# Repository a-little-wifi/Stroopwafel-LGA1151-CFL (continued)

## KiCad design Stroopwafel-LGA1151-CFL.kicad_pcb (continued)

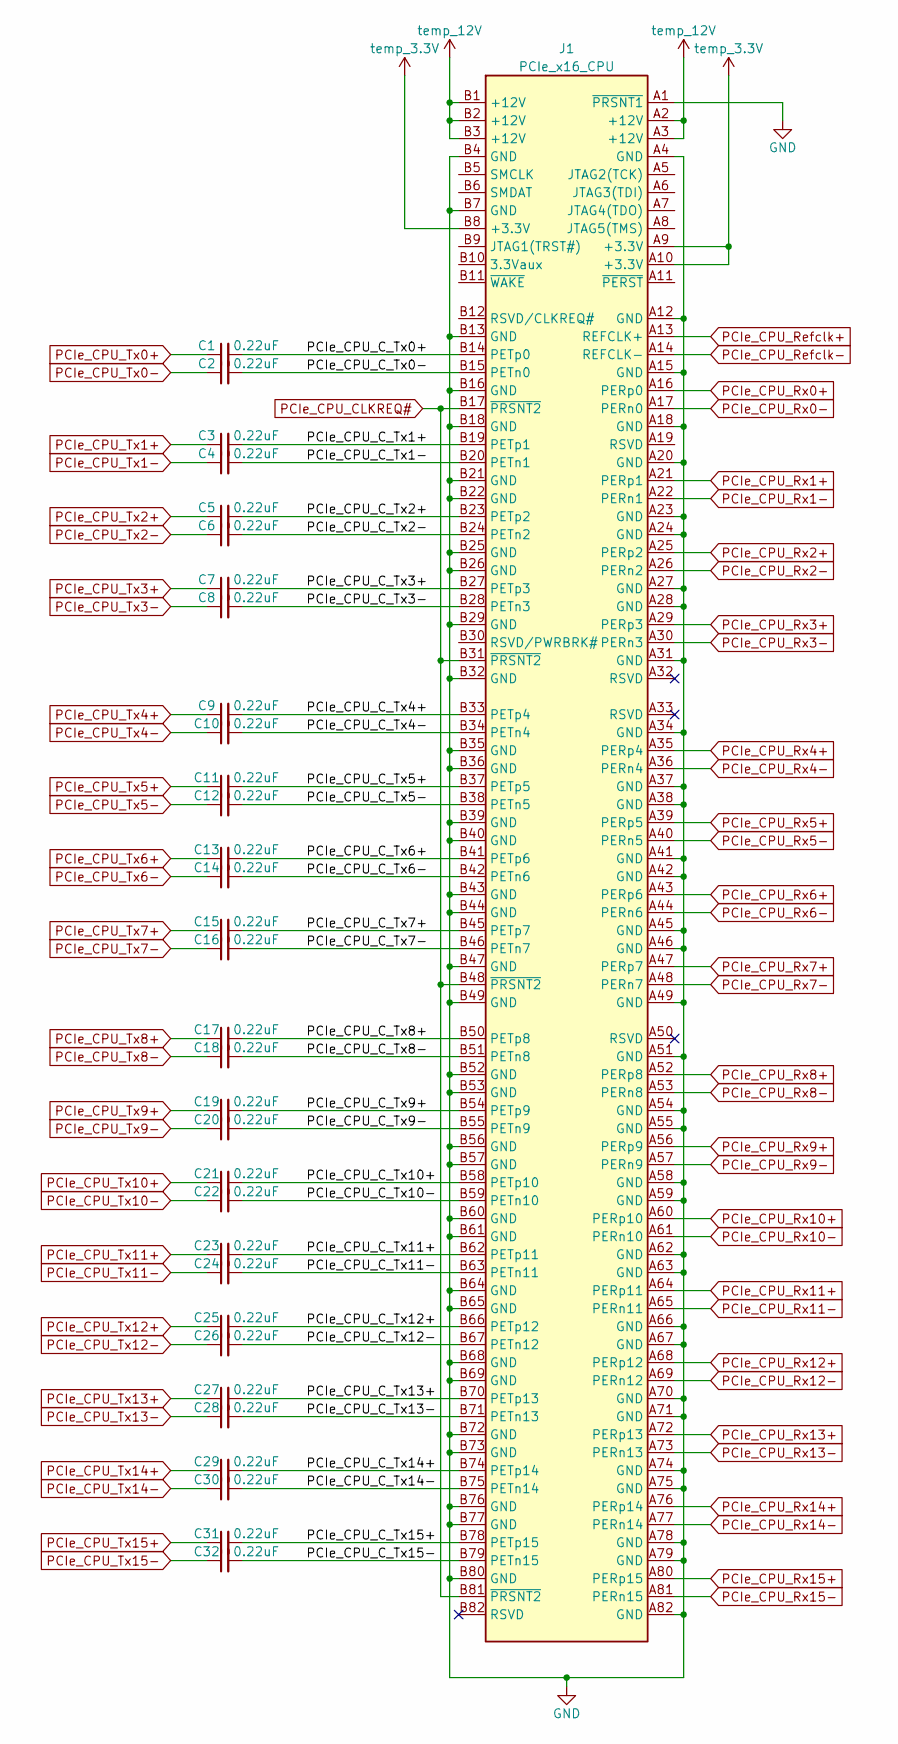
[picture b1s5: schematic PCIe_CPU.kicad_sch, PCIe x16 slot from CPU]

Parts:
C1, C2, C3, C4, C5, C6, C7, C8, C9, C10, C11, C12, C13, C14, C15, C16, C17, C18, C19, C20, C21, C22, C23, C24, C25, C26, C27, C28, C29, C30, C31, C32: 0.22uF; C_0402_1005Metric
J1: PCIe_x16_CPU; PCIe_x16_tht_smallholes

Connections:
/PCIe_CPU/PCIe_CPU_C_Tx0+: C1.2, J1.B14 (PETp0)
/PCIe_CPU/PCIe_CPU_C_Tx0-: C2.2, J1.B15 (PETn0)
/PCIe_CPU/PCIe_CPU_C_Tx1+: C3.2, J1.B19 (PETp1)
/PCIe_CPU/PCIe_CPU_C_Tx1-: C4.2, J1.B20 (PETn1)
/PCIe_CPU/PCIe_CPU_C_Tx2+: C5.2, J1.B23 (PETp2)
/PCIe_CPU/PCIe_CPU_C_Tx2-: C6.2, J1.B24 (PETn2)
/PCIe_CPU/PCIe_CPU_C_Tx3+: C7.2, J1.B27 (PETp3)
/PCIe_CPU/PCIe_CPU_C_Tx3-: C8.2, J1.B28 (PETn3)
/PCIe_CPU/PCIe_CPU_C_Tx4+: C9.2, J1.B33 (PETp4)
/PCIe_CPU/PCIe_CPU_C_Tx4-: C10.2, J1.B34 (PETn4)
/PCIe_CPU/PCIe_CPU_C_Tx5+: C11.2, J1.B37 (PETp5)
/PCIe_CPU/PCIe_CPU_C_Tx5-: C12.2, J1.B38 (PETn5)
/PCIe_CPU/PCIe_CPU_C_Tx6+: C13.2, J1.B41 (PETp6)
/PCIe_CPU/PCIe_CPU_C_Tx6-: C14.2, J1.B42 (PETn6)
/PCIe_CPU/PCIe_CPU_C_Tx7+: C15.2, J1.B45 (PETp7)
/PCIe_CPU/PCIe_CPU_C_Tx7-: C16.2, J1.B46 (PETn7)
/PCIe_CPU/PCIe_CPU_C_Tx8+: C17.2, J1.B50 (PETp8)
/PCIe_CPU/PCIe_CPU_C_Tx8-: C18.2, J1.B51 (PETn8)
/PCIe_CPU/PCIe_CPU_C_Tx9+: C19.2, J1.B54 (PETp9)
/PCIe_CPU/PCIe_CPU_C_Tx9-: C20.2, J1.B55 (PETn9)
/PCIe_CPU/PCIe_CPU_C_Tx10+: C21.2, J1.B58 (PETp10)
/PCIe_CPU/PCIe_CPU_C_Tx10-: C22.2, J1.B59 (PETn10)
/PCIe_CPU/PCIe_CPU_C_Tx11+: C23.2, J1.B62 (PETp11)
/PCIe_CPU/PCIe_CPU_C_Tx11-: C24.2, J1.B63 (PETn11)
/PCIe_CPU/PCIe_CPU_C_Tx12+: C25.2, J1.B66 (PETp12)
/PCIe_CPU/PCIe_CPU_C_Tx12-: C26.2, J1.B67 (PETn12)
/PCIe_CPU/PCIe_CPU_C_Tx13+: C27.2, J1.B70 (PETp13)
/PCIe_CPU/PCIe_CPU_C_Tx13-: C28.2, J1.B71 (PETn13)
/PCIe_CPU/PCIe_CPU_C_Tx14+: C29.2, J1.B74 (PETp14)
/PCIe_CPU/PCIe_CPU_C_Tx14-: C30.2, J1.B75 (PETn14)
/PCIe_CPU/PCIe_CPU_C_Tx15+: C31.2, J1.B78 (PETp15)
/PCIe_CPU/PCIe_CPU_C_Tx15-: C32.2, J1.B79 (PETn15)
GND: J1.A1 (~PRSNT1), J1.A4 (GND), J1.A12 (GND), J1.A15 (GND), J1.A18 (GND), J1.A20 (GND), J1.A23 (GND), J1.A24 (GND), J1.A27 (GND), J1.A28 (GND), J1.A31 (GND), J1.A34 (GND), J1.A37 (GND), J1.A38 (GND), J1.A41 (GND), J1.A42 (GND), J1.A45 (GND), J1.A46 (GND), J1.A49 (GND), J1.A51 (GND), J1.A54 (GND), J1.A55 (GND), J1.A58 (GND), J1.A59 (GND), J1.A62 (GND), J1.A63 (GND), J1.A66 (GND), J1.A67 (GND), J1.A70 (GND), J1.A71 (GND), J1.A74 (GND), J1.A75 (GND), J1.A78 (GND), J1.A79 (GND), J1.A82 (GND), J1.B4 (GND), J1.B7 (GND), J1.B13 (GND), J1.B16 (GND), J1.B18 (GND), J1.B21 (GND), J1.B22 (GND), J1.B25 (GND), J1.B26 (GND), J1.B29 (GND), J1.B32 (GND), J1.B35 (GND), J1.B36 (GND), J1.B39 (GND), J1.B40 (GND), J1.B43 (GND), J1.B44 (GND), J1.B47 (GND), J1.B49 (GND), J1.B52 (GND), J1.B53 (GND), J1.B56 (GND), J1.B57 (GND), J1.B60 (GND), J1.B61 (GND), J1.B64 (GND), J1.B65 (GND), J1.B68 (GND), J1.B69 (GND), J1.B72 (GND), J1.B73 (GND), J1.B76 (GND), J1.B77 (GND), J1.B80 (GND); also elsewhere on the board
PCIe_CPU_CLKREQ#: J1.B17 (~PRSNT2), J1.B31 (~PRSNT2), J1.B48 (~PRSNT2), J1.B81 (~PRSNT2); also elsewhere on the board
PCIe_CPU_Refclk+: J1.A13 (REFCLK+); also elsewhere on the board
PCIe_CPU_Refclk-: J1.A14 (REFCLK-); also elsewhere on the board
PCIe_CPU_Rx0+: J1.A16 (PERp0); also elsewhere on the board
PCIe_CPU_Rx0-: J1.A17 (PERn0); also elsewhere on the board
PCIe_CPU_Rx1+: J1.A21 (PERp1); also elsewhere on the board
PCIe_CPU_Rx1-: J1.A22 (PERn1); also elsewhere on the board
PCIe_CPU_Rx2+: J1.A25 (PERp2); also elsewhere on the board
PCIe_CPU_Rx2-: J1.A26 (PERn2); also elsewhere on the board
PCIe_CPU_Rx3+: J1.A29 (PERp3); also elsewhere on the board
PCIe_CPU_Rx3-: J1.A30 (PERn3); also elsewhere on the board
PCIe_CPU_Rx4+: J1.A35 (PERp4); also elsewhere on the board
PCIe_CPU_Rx4-: J1.A36 (PERn4); also elsewhere on the board
PCIe_CPU_Rx5+: J1.A39 (PERp5); also elsewhere on the board
PCIe_CPU_Rx5-: J1.A40 (PERn5); also elsewhere on the board
PCIe_CPU_Rx6+: J1.A43 (PERp6); also elsewhere on the board
PCIe_CPU_Rx6-: J1.A44 (PERn6); also elsewhere on the board
PCIe_CPU_Rx7+: J1.A47 (PERp7); also elsewhere on the board
PCIe_CPU_Rx7-: J1.A48 (PERn7); also elsewhere on the board
PCIe_CPU_Rx8+: J1.A52 (PERp8); also elsewhere on the board
PCIe_CPU_Rx8-: J1.A53 (PERn8); also elsewhere on the board
PCIe_CPU_Rx9+: J1.A56 (PERp9); also elsewhere on the board
PCIe_CPU_Rx9-: J1.A57 (PERn9); also elsewhere on the board
PCIe_CPU_Rx10+: J1.A60 (PERp10); also elsewhere on the board
PCIe_CPU_Rx10-: J1.A61 (PERn10); also elsewhere on the board
PCIe_CPU_Rx11+: J1.A64 (PERp11); also elsewhere on the board
PCIe_CPU_Rx11-: J1.A65 (PERn11); also elsewhere on the board
PCIe_CPU_Rx12+: J1.A68 (PERp12); also elsewhere on the board
PCIe_CPU_Rx12-: J1.A69 (PERn12); also elsewhere on the board
PCIe_CPU_Rx13+: J1.A72 (PERp13); also elsewhere on the board
PCIe_CPU_Rx13-: J1.A73 (PERn13); also elsewhere on the board
PCIe_CPU_Rx14+: J1.A76 (PERp14); also elsewhere on the board
PCIe_CPU_Rx14-: J1.A77 (PERn14); also elsewhere on the board
PCIe_CPU_Rx15+: J1.A80 (PERp15); also elsewhere on the board
PCIe_CPU_Rx15-: J1.A81 (PERn15); also elsewhere on the board
PCIe_CPU_Tx0+: C1.1; also elsewhere on the board
PCIe_CPU_Tx0-: C2.1; also elsewhere on the board
PCIe_CPU_Tx1+: C3.1; also elsewhere on the board
PCIe_CPU_Tx1-: C4.1; also elsewhere on the board
PCIe_CPU_Tx2+: C5.1; also elsewhere on the board
PCIe_CPU_Tx2-: C6.1; also elsewhere on the board
PCIe_CPU_Tx3+: C7.1; also elsewhere on the board
PCIe_CPU_Tx3-: C8.1; also elsewhere on the board
PCIe_CPU_Tx4+: C9.1; also elsewhere on the board
PCIe_CPU_Tx4-: C10.1; also elsewhere on the board
PCIe_CPU_Tx5+: C11.1; also elsewhere on the board
PCIe_CPU_Tx5-: C12.1; also elsewhere on the board
PCIe_CPU_Tx6+: C13.1; also elsewhere on the board
PCIe_CPU_Tx6-: C14.1; also elsewhere on the board
PCIe_CPU_Tx7+: C15.1; also elsewhere on the board
PCIe_CPU_Tx7-: C16.1; also elsewhere on the board
PCIe_CPU_Tx8+: C17.1; also elsewhere on the board
PCIe_CPU_Tx8-: C18.1; also elsewhere on the board
PCIe_CPU_Tx9+: C19.1; also elsewhere on the board
PCIe_CPU_Tx9-: C20.1; also elsewhere on the board
PCIe_CPU_Tx10+: C21.1; also elsewhere on the board
PCIe_CPU_Tx10-: C22.1; also elsewhere on the board
PCIe_CPU_Tx11+: C23.1; also elsewhere on the board
PCIe_CPU_Tx11-: C24.1; also elsewhere on the board
PCIe_CPU_Tx12+: C25.1; also elsewhere on the board
PCIe_CPU_Tx12-: C26.1; also elsewhere on the board
PCIe_CPU_Tx13+: C27.1; also elsewhere on the board
PCIe_CPU_Tx13-: C28.1; also elsewhere on the board
PCIe_CPU_Tx14+: C29.1; also elsewhere on the board
PCIe_CPU_Tx14-: C30.1; also elsewhere on the board
PCIe_CPU_Tx15+: C31.1; also elsewhere on the board
PCIe_CPU_Tx15-: C32.1; also elsewhere on the board
temp_3.3V: J1.A9 (+3.3V), J1.A10 (+3.3V), J1.B8 (+3.3V); also elsewhere on the board
temp_12V: J1.A2 (+12V), J1.A3 (+12V), J1.B1 (+12V), J1.B2 (+12V), J1.B3 (+12V); also elsewhere on the board

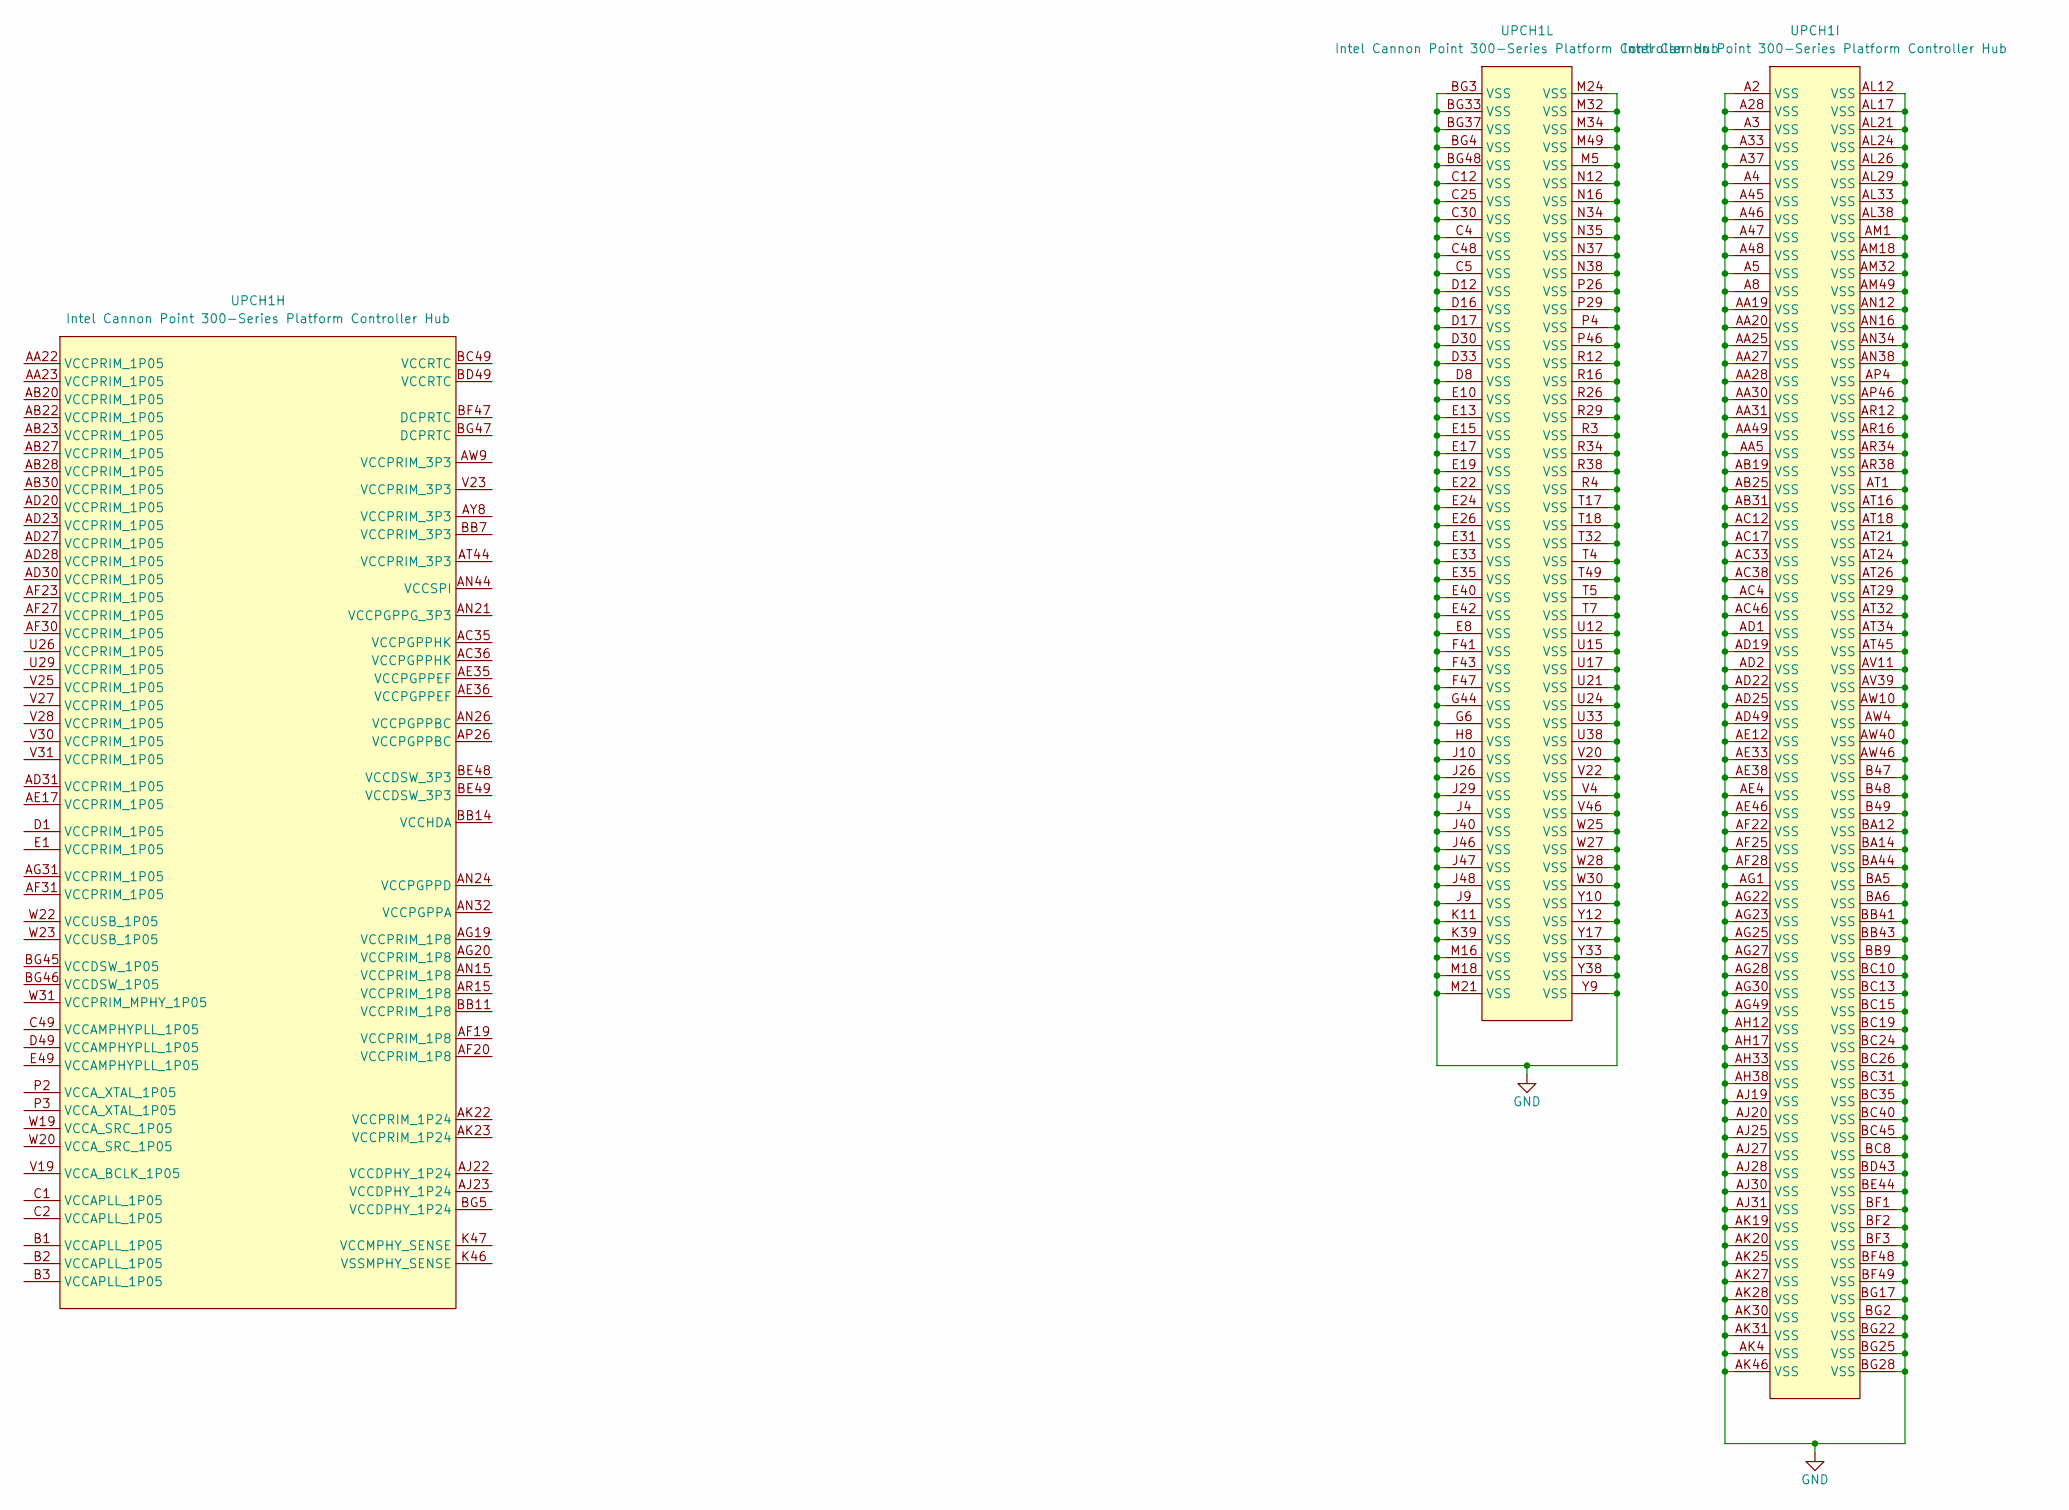
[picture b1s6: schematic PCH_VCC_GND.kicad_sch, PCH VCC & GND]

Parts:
UPCH1: Intel Cannon Point 300-Series Platform Controller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; CNP-H_BGA_874P-T

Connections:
GND: UPCH1.A2 (VSS), UPCH1.A3 (VSS), UPCH1.A4 (VSS), UPCH1.A5 (VSS), UPCH1.A8 (VSS), UPCH1.A28 (VSS), UPCH1.A33 (VSS), UPCH1.A37 (VSS), UPCH1.A45 (VSS), UPCH1.A46 (VSS), UPCH1.A47 (VSS), UPCH1.A48 (VSS), UPCH1.AA5 (VSS), UPCH1.AA19 (VSS), UPCH1.AA20 (VSS), UPCH1.AA25 (VSS), UPCH1.AA27 (VSS), UPCH1.AA28 (VSS), UPCH1.AA30 (VSS), UPCH1.AA31 (VSS), UPCH1.AA49 (VSS), UPCH1.AB19 (VSS), UPCH1.AB25 (VSS), UPCH1.AB31 (VSS), UPCH1.AC4 (VSS), UPCH1.AC12 (VSS), UPCH1.AC17 (VSS), UPCH1.AC33 (VSS), UPCH1.AC38 (VSS), UPCH1.AC46 (VSS), UPCH1.AD1 (VSS), UPCH1.AD2 (VSS), UPCH1.AD19 (VSS), UPCH1.AD22 (VSS), UPCH1.AD25 (VSS), UPCH1.AD49 (VSS), UPCH1.AE4 (VSS), UPCH1.AE12 (VSS), UPCH1.AE33 (VSS), UPCH1.AE38 (VSS), UPCH1.AE46 (VSS), UPCH1.AF22 (VSS), UPCH1.AF25 (VSS), UPCH1.AF28 (VSS), UPCH1.AG1 (VSS), UPCH1.AG22 (VSS), UPCH1.AG23 (VSS), UPCH1.AG25 (VSS), UPCH1.AG27 (VSS), UPCH1.AG28 (VSS), UPCH1.AG30 (VSS), UPCH1.AG49 (VSS), UPCH1.AH12 (VSS), UPCH1.AH17 (VSS), UPCH1.AH33 (VSS), UPCH1.AH38 (VSS), UPCH1.AJ19 (VSS), UPCH1.AJ20 (VSS), UPCH1.AJ25 (VSS), UPCH1.AJ27 (VSS), UPCH1.AJ28 (VSS), UPCH1.AJ30 (VSS), UPCH1.AJ31 (VSS), UPCH1.AK4 (VSS), UPCH1.AK19 (VSS), UPCH1.AK20 (VSS), UPCH1.AK25 (VSS), UPCH1.AK27 (VSS), UPCH1.AK28 (VSS), UPCH1.AK30 (VSS), UPCH1.AK31 (VSS), UPCH1.AK46 (VSS), UPCH1.AL12 (VSS), UPCH1.AL17 (VSS), UPCH1.AL21 (VSS), UPCH1.AL24 (VSS), UPCH1.AL26 (VSS), UPCH1.AL29 (VSS), UPCH1.AL33 (VSS), UPCH1.AL38 (VSS), UPCH1.AM1 (VSS), UPCH1.AM18 (VSS), UPCH1.AM32 (VSS), UPCH1.AM49 (VSS), UPCH1.AN12 (VSS), UPCH1.AN16 (VSS), UPCH1.AN34 (VSS), UPCH1.AN38 (VSS), UPCH1.AP4 (VSS), UPCH1.AP46 (VSS), UPCH1.AR12 (VSS), UPCH1.AR16 (VSS), UPCH1.AR34 (VSS), UPCH1.AR38 (VSS), UPCH1.AT1 (VSS), UPCH1.AT16 (VSS), UPCH1.AT18 (VSS), UPCH1.AT21 (VSS), UPCH1.AT24 (VSS), UPCH1.AT26 (VSS), UPCH1.AT29 (VSS), UPCH1.AT32 (VSS), UPCH1.AT34 (VSS), UPCH1.AT45 (VSS), UPCH1.AV11 (VSS), UPCH1.AV39 (VSS), UPCH1.AW4 (VSS), UPCH1.AW10 (VSS), UPCH1.AW40 (VSS), UPCH1.AW46 (VSS), UPCH1.B47 (VSS), UPCH1.B48 (VSS), UPCH1.B49 (VSS), UPCH1.BA5 (VSS), UPCH1.BA6 (VSS), UPCH1.BA12 (VSS), UPCH1.BA14 (VSS), UPCH1.BA44 (VSS), UPCH1.BB9 (VSS), UPCH1.BB41 (VSS), UPCH1.BB43 (VSS), UPCH1.BC8 (VSS), UPCH1.BC10 (VSS), UPCH1.BC13 (VSS), UPCH1.BC15 (VSS), UPCH1.BC19 (VSS), UPCH1.BC24 (VSS), UPCH1.BC26 (VSS), UPCH1.BC31 (VSS)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; also elsewhere on the board

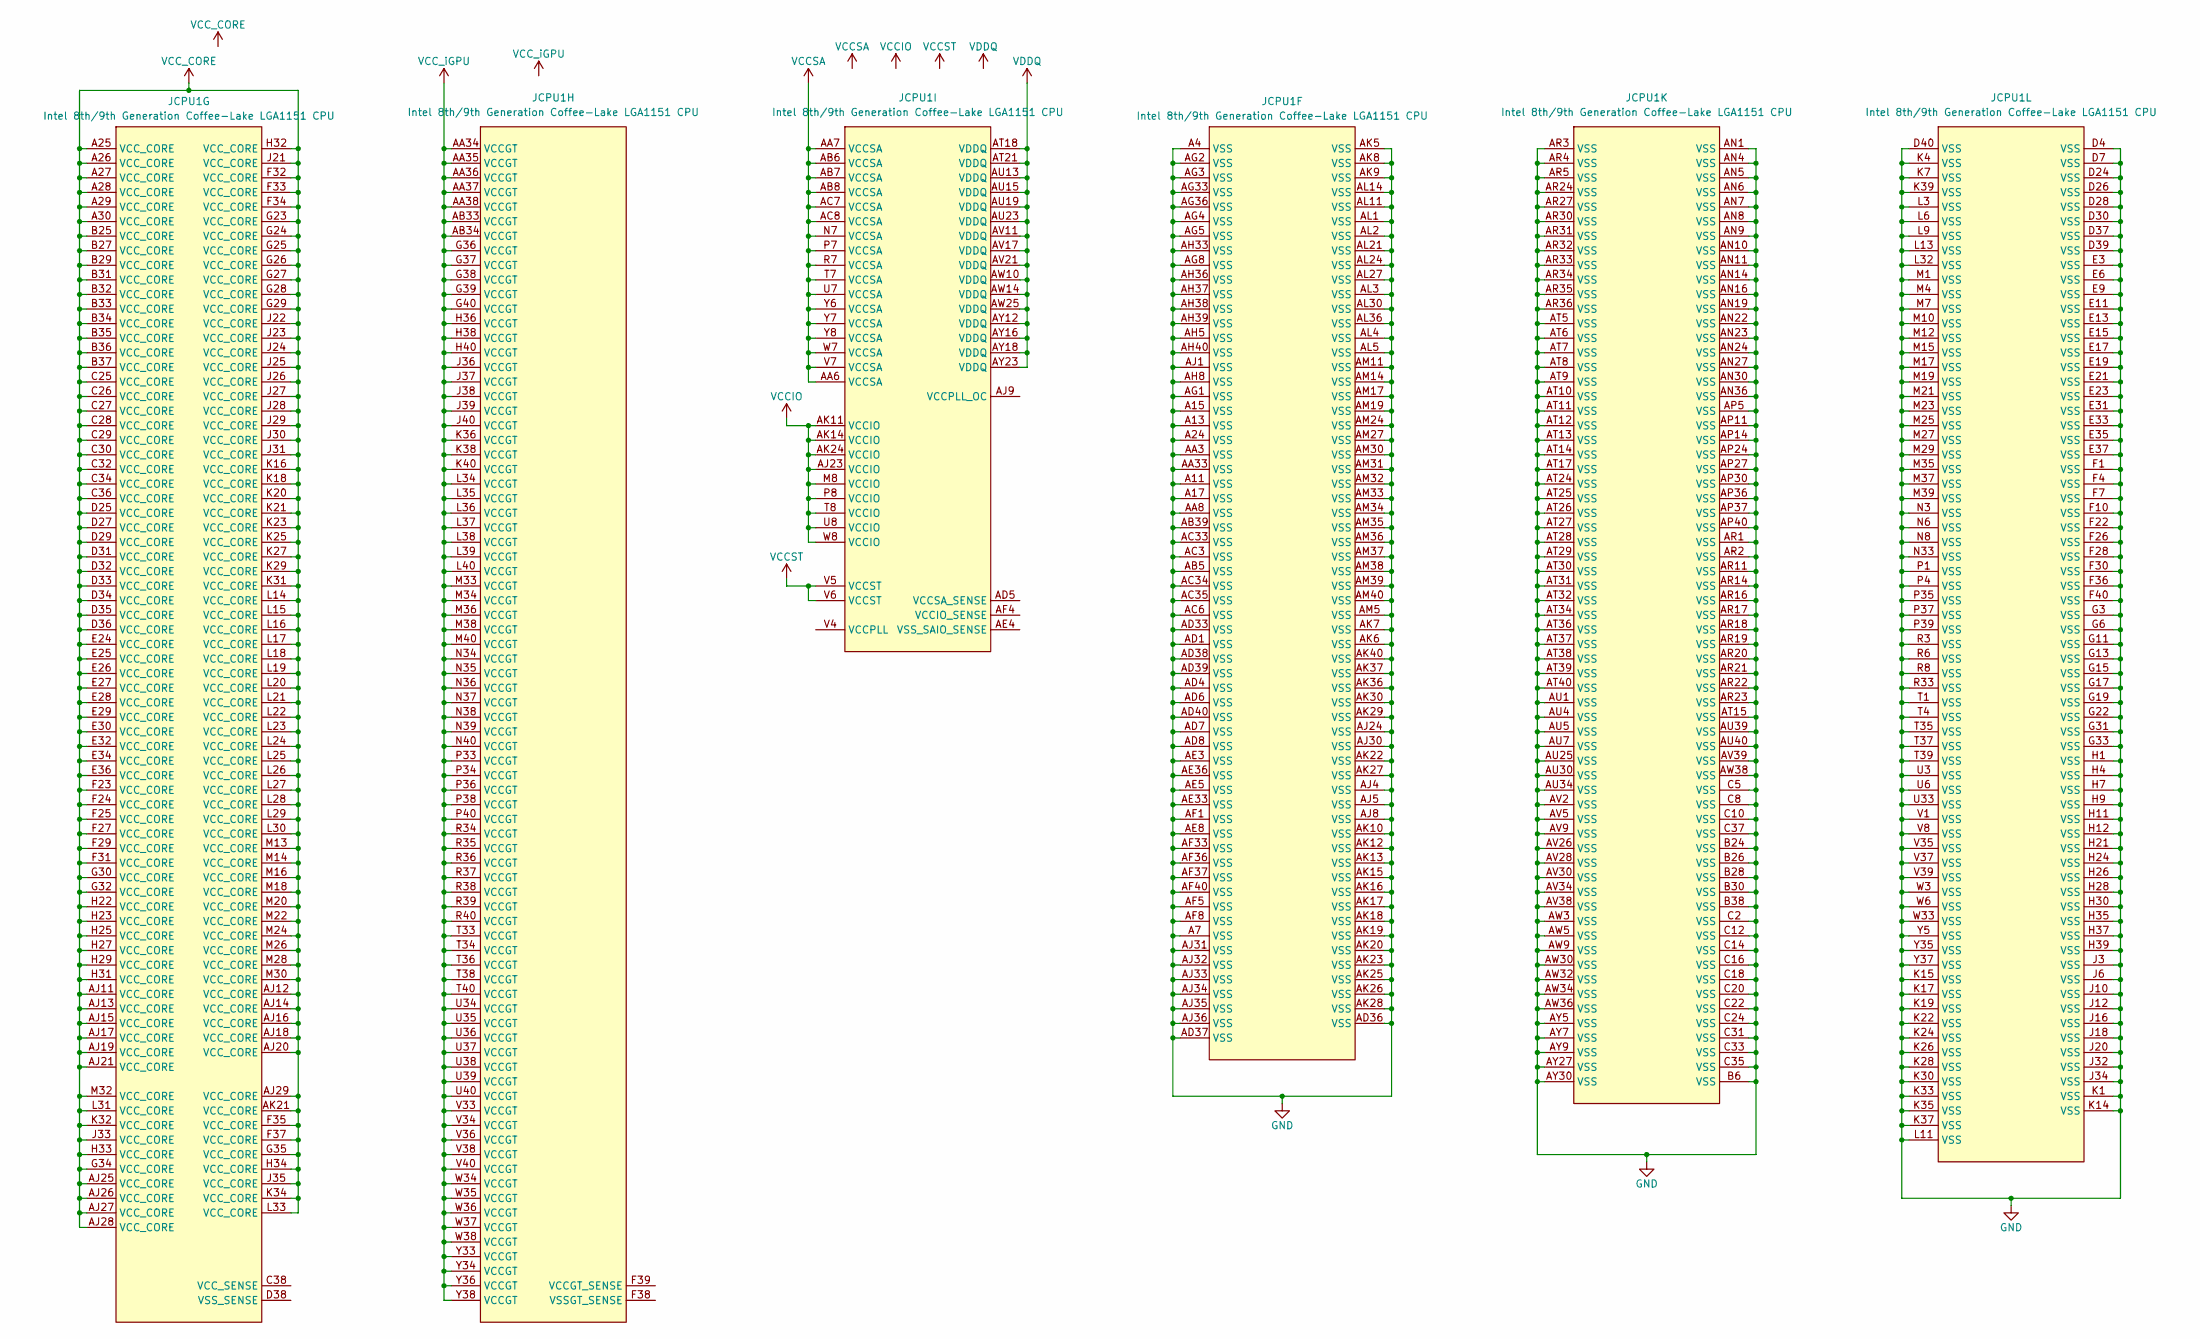
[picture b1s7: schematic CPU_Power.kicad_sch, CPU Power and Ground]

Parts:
JCPU1: Intel 8th/9th Generation Coffee-Lake LGA1151 CPU; LGA-1151_L47.1-W42.5-P0.91_PE115127-4041-01H

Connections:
GND: JCPU1.A4 (VSS), JCPU1.A7 (VSS), JCPU1.A11 (VSS), JCPU1.A13 (VSS), JCPU1.A15 (VSS), JCPU1.A17 (VSS), JCPU1.A24 (VSS), JCPU1.AA3 (VSS), JCPU1.AA8 (VSS), JCPU1.AA33 (VSS), JCPU1.AB5 (VSS), JCPU1.AB39 (VSS), JCPU1.AC3 (VSS), JCPU1.AC6 (VSS), JCPU1.AC33 (VSS), JCPU1.AC34 (VSS), JCPU1.AC35 (VSS), JCPU1.AD1 (VSS), JCPU1.AD4 (VSS), JCPU1.AD6 (VSS), JCPU1.AD7 (VSS), JCPU1.AD8 (VSS), JCPU1.AD33 (VSS), JCPU1.AD36 (VSS), JCPU1.AD37 (VSS), JCPU1.AD38 (VSS), JCPU1.AD39 (VSS), JCPU1.AD40 (VSS), JCPU1.AE3 (VSS), JCPU1.AE5 (VSS), JCPU1.AE8 (VSS), JCPU1.AE33 (VSS), JCPU1.AE36 (VSS), JCPU1.AF1 (VSS), JCPU1.AF5 (VSS), JCPU1.AF8 (VSS), JCPU1.AF33 (VSS), JCPU1.AF36 (VSS), JCPU1.AF37 (VSS), JCPU1.AF40 (VSS), JCPU1.AG1 (VSS), JCPU1.AG2 (VSS), JCPU1.AG3 (VSS), JCPU1.AG4 (VSS), JCPU1.AG5 (VSS), JCPU1.AG8 (VSS), JCPU1.AG33 (VSS), JCPU1.AG36 (VSS), JCPU1.AH5 (VSS), JCPU1.AH8 (VSS), JCPU1.AH33 (VSS), JCPU1.AH36 (VSS), JCPU1.AH37 (VSS), JCPU1.AH38 (VSS), JCPU1.AH39 (VSS), JCPU1.AH40 (VSS), JCPU1.AJ1 (VSS), JCPU1.AJ4 (VSS), JCPU1.AJ5 (VSS), JCPU1.AJ8 (VSS), JCPU1.AJ24 (VSS), JCPU1.AJ30 (VSS), JCPU1.AJ31 (VSS), JCPU1.AJ32 (VSS), JCPU1.AJ33 (VSS), JCPU1.AJ34 (VSS), JCPU1.AJ35 (VSS), JCPU1.AJ36 (VSS), JCPU1.AK5 (VSS), JCPU1.AK6 (VSS), JCPU1.AK7 (VSS), JCPU1.AK8 (VSS), JCPU1.AK9 (VSS), JCPU1.AK10 (VSS), JCPU1.AK12 (VSS), JCPU1.AK13 (VSS), JCPU1.AK15 (VSS), JCPU1.AK16 (VSS), JCPU1.AK17 (VSS), JCPU1.AK18 (VSS), JCPU1.AK19 (VSS), JCPU1.AK20 (VSS), JCPU1.AK22 (VSS), JCPU1.AK23 (VSS), JCPU1.AK25 (VSS), JCPU1.AK26 (VSS), JCPU1.AK27 (VSS), JCPU1.AK28 (VSS), JCPU1.AK29 (VSS), JCPU1.AK30 (VSS), JCPU1.AK36 (VSS), JCPU1.AK37 (VSS), JCPU1.AK40 (VSS), JCPU1.AL1 (VSS), JCPU1.AL2 (VSS), JCPU1.AL3 (VSS), JCPU1.AL4 (VSS), JCPU1.AL5 (VSS), JCPU1.AL11 (VSS), JCPU1.AL14 (VSS), JCPU1.AL21 (VSS), JCPU1.AL24 (VSS), JCPU1.AL27 (VSS), JCPU1.AL30 (VSS), JCPU1.AL36 (VSS), JCPU1.AM5 (VSS), JCPU1.AM11 (VSS), JCPU1.AM14 (VSS), JCPU1.AM17 (VSS), JCPU1.AM19 (VSS), JCPU1.AM24 (VSS), JCPU1.AM27 (VSS), JCPU1.AM30 (VSS), JCPU1.AM31 (VSS), JCPU1.AM32 (VSS), JCPU1.AM33 (VSS), JCPU1.AM34 (VSS), JCPU1.AM35 (VSS), JCPU1.AM36 (VSS), JCPU1.AM37 (VSS), JCPU1.AM38 (VSS), JCPU1.AM39 (VSS), JCPU1.AM40 (VSS), JCPU1.AN1 (VSS), JCPU1.AN4 (VSS), JCPU1.AN5 (VSS), JCPU1.AN6 (VSS), JCPU1.AN7 (VSS), JCPU1.AN8 (VSS)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; also elsewhere on the board
VCCIO: JCPU1.AJ23 (VCCIO), JCPU1.AK11 (VCCIO), JCPU1.AK14 (VCCIO), JCPU1.AK24 (VCCIO), JCPU1.M8 (VCCIO), JCPU1.P8 (VCCIO), JCPU1.T8 (VCCIO), JCPU1.U8 (VCCIO), JCPU1.W8 (VCCIO); also elsewhere on the board
VCCSA: JCPU1.AA6 (VCCSA), JCPU1.AA7 (VCCSA), JCPU1.AB6 (VCCSA), JCPU1.AB7 (VCCSA), JCPU1.AB8 (VCCSA), JCPU1.AC7 (VCCSA), JCPU1.AC8 (VCCSA), JCPU1.N7 (VCCSA), JCPU1.P7 (VCCSA), JCPU1.R7 (VCCSA), JCPU1.T7 (VCCSA), JCPU1.U7 (VCCSA), JCPU1.V7 (VCCSA), JCPU1.W7 (VCCSA), JCPU1.Y6 (VCCSA), JCPU1.Y7 (VCCSA), JCPU1.Y8 (VCCSA)
VCCST: JCPU1.V5 (VCCST), JCPU1.V6 (VCCST); also elsewhere on the board
VCC_CORE: JCPU1.A25 (VCC_CORE), JCPU1.A26 (VCC_CORE), JCPU1.A27 (VCC_CORE), JCPU1.A28 (VCC_CORE), JCPU1.A29 (VCC_CORE), JCPU1.A30 (VCC_CORE), JCPU1.AJ11 (VCC_CORE), JCPU1.AJ12 (VCC_CORE), JCPU1.AJ13 (VCC_CORE), JCPU1.AJ14 (VCC_CORE), JCPU1.AJ15 (VCC_CORE), JCPU1.AJ16 (VCC_CORE), JCPU1.AJ17 (VCC_CORE), JCPU1.AJ18 (VCC_CORE), JCPU1.AJ19 (VCC_CORE), JCPU1.AJ20 (VCC_CORE), JCPU1.AJ21 (VCC_CORE), JCPU1.AJ25 (VCC_CORE), JCPU1.AJ26 (VCC_CORE), JCPU1.AJ27 (VCC_CORE), JCPU1.AJ28 (VCC_CORE), JCPU1.AJ29 (VCC_CORE), JCPU1.AK21 (VCC_CORE), JCPU1.B25 (VCC_CORE), JCPU1.B27 (VCC_CORE), JCPU1.B29 (VCC_CORE), JCPU1.B31 (VCC_CORE), JCPU1.B32 (VCC_CORE), JCPU1.B33 (VCC_CORE), JCPU1.B34 (VCC_CORE), JCPU1.B35 (VCC_CORE), JCPU1.B36 (VCC_CORE), JCPU1.B37 (VCC_CORE), JCPU1.C25 (VCC_CORE), JCPU1.C26 (VCC_CORE), JCPU1.C27 (VCC_CORE), JCPU1.C28 (VCC_CORE), JCPU1.C29 (VCC_CORE), JCPU1.C30 (VCC_CORE), JCPU1.C32 (VCC_CORE), JCPU1.C34 (VCC_CORE), JCPU1.C36 (VCC_CORE), JCPU1.D25 (VCC_CORE), JCPU1.D27 (VCC_CORE), JCPU1.D29 (VCC_CORE), JCPU1.D31 (VCC_CORE), JCPU1.D32 (VCC_CORE), JCPU1.D33 (VCC_CORE), JCPU1.D34 (VCC_CORE), JCPU1.D35 (VCC_CORE), JCPU1.D36 (VCC_CORE), JCPU1.E24 (VCC_CORE), JCPU1.E25 (VCC_CORE), JCPU1.E26 (VCC_CORE), JCPU1.E27 (VCC_CORE), JCPU1.E28 (VCC_CORE), JCPU1.E29 (VCC_CORE), JCPU1.E30 (VCC_CORE), JCPU1.E32 (VCC_CORE), JCPU1.E34 (VCC_CORE), JCPU1.E36 (VCC_CORE), JCPU1.F23 (VCC_CORE), JCPU1.F24 (VCC_CORE), JCPU1.F25 (VCC_CORE), JCPU1.F27 (VCC_CORE), JCPU1.F29 (VCC_CORE), JCPU1.F31 (VCC_CORE), JCPU1.F32 (VCC_CORE), JCPU1.F33 (VCC_CORE), JCPU1.F34 (VCC_CORE), JCPU1.F35 (VCC_CORE), JCPU1.F37 (VCC_CORE), JCPU1.G23 (VCC_CORE), JCPU1.G24 (VCC_CORE), JCPU1.G25 (VCC_CORE), JCPU1.G26 (VCC_CORE), JCPU1.G27 (VCC_CORE), JCPU1.G28 (VCC_CORE), JCPU1.G29 (VCC_CORE), JCPU1.G30 (VCC_CORE), JCPU1.G32 (VCC_CORE), JCPU1.G34 (VCC_CORE), JCPU1.G35 (VCC_CORE), JCPU1.H22 (VCC_CORE), JCPU1.H23 (VCC_CORE), JCPU1.H25 (VCC_CORE), JCPU1.H27 (VCC_CORE), JCPU1.H29 (VCC_CORE), JCPU1.H31 (VCC_CORE), JCPU1.H32 (VCC_CORE), JCPU1.H33 (VCC_CORE), JCPU1.H34 (VCC_CORE), JCPU1.J21 (VCC_CORE), JCPU1.J22 (VCC_CORE), JCPU1.J23 (VCC_CORE), JCPU1.J24 (VCC_CORE), JCPU1.J25 (VCC_CORE), JCPU1.J26 (VCC_CORE), JCPU1.J27 (VCC_CORE), JCPU1.J28 (VCC_CORE), JCPU1.J29 (VCC_CORE), JCPU1.J30 (VCC_CORE), JCPU1.J31 (VCC_CORE), JCPU1.J33 (VCC_CORE), JCPU1.J35 (VCC_CORE), JCPU1.K16 (VCC_CORE), JCPU1.K18 (VCC_CORE), JCPU1.K20 (VCC_CORE), JCPU1.K21 (VCC_CORE), JCPU1.K23 (VCC_CORE), JCPU1.K25 (VCC_CORE), JCPU1.K27 (VCC_CORE), JCPU1.K29 (VCC_CORE), JCPU1.K31 (VCC_CORE), JCPU1.K32 (VCC_CORE), JCPU1.K34 (VCC_CORE), JCPU1.L14 (VCC_CORE), JCPU1.L15 (VCC_CORE), JCPU1.L16 (VCC_CORE), JCPU1.L17 (VCC_CORE), JCPU1.L18 (VCC_CORE), JCPU1.L19 (VCC_CORE), JCPU1.L20 (VCC_CORE), JCPU1.L21 (VCC_CORE), JCPU1.L22 (VCC_CORE), JCPU1.L23 (VCC_CORE), JCPU1.L24 (VCC_CORE), JCPU1.L25 (VCC_CORE), JCPU1.L26 (VCC_CORE)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
VCC_iGPU: JCPU1.AA34 (VCCGT), JCPU1.AA35 (VCCGT), JCPU1.AA36 (VCCGT), JCPU1.AA37 (VCCGT), JCPU1.AA38 (VCCGT), JCPU1.AB33 (VCCGT), JCPU1.AB34 (VCCGT), JCPU1.G36 (VCCGT), JCPU1.G37 (VCCGT), JCPU1.G38 (VCCGT), JCPU1.G39 (VCCGT), JCPU1.G40 (VCCGT), JCPU1.H36 (VCCGT), JCPU1.H38 (VCCGT), JCPU1.H40 (VCCGT), JCPU1.J36 (VCCGT), JCPU1.J37 (VCCGT), JCPU1.J38 (VCCGT), JCPU1.J39 (VCCGT), JCPU1.J40 (VCCGT), JCPU1.K36 (VCCGT), JCPU1.K38 (VCCGT), JCPU1.K40 (VCCGT), JCPU1.L34 (VCCGT), JCPU1.L35 (VCCGT), JCPU1.L36 (VCCGT), JCPU1.L37 (VCCGT), JCPU1.L38 (VCCGT), JCPU1.L39 (VCCGT), JCPU1.L40 (VCCGT), JCPU1.M33 (VCCGT), JCPU1.M34 (VCCGT), JCPU1.M36 (VCCGT), JCPU1.M38 (VCCGT), JCPU1.M40 (VCCGT), JCPU1.N34 (VCCGT), JCPU1.N35 (VCCGT), JCPU1.N36 (VCCGT), JCPU1.N37 (VCCGT), JCPU1.N38 (VCCGT), JCPU1.N39 (VCCGT), JCPU1.N40 (VCCGT), JCPU1.P33 (VCCGT), JCPU1.P34 (VCCGT), JCPU1.P36 (VCCGT), JCPU1.P38 (VCCGT), JCPU1.P40 (VCCGT), JCPU1.R34 (VCCGT), JCPU1.R35 (VCCGT), JCPU1.R36 (VCCGT), JCPU1.R37 (VCCGT), JCPU1.R38 (VCCGT), JCPU1.R39 (VCCGT), JCPU1.R40 (VCCGT), JCPU1.T33 (VCCGT), JCPU1.T34 (VCCGT), JCPU1.T36 (VCCGT), JCPU1.T38 (VCCGT), JCPU1.T40 (VCCGT), JCPU1.U34 (VCCGT), JCPU1.U35 (VCCGT), JCPU1.U36 (VCCGT), JCPU1.U37 (VCCGT), JCPU1.U38 (VCCGT), JCPU1.U39 (VCCGT), JCPU1.U40 (VCCGT), JCPU1.V33 (VCCGT), JCPU1.V34 (VCCGT), JCPU1.V36 (VCCGT), JCPU1.V38 (VCCGT), JCPU1.V40 (VCCGT), JCPU1.W34 (VCCGT), JCPU1.W35 (VCCGT), JCPU1.W36 (VCCGT), JCPU1.W37 (VCCGT), JCPU1.W38 (VCCGT), JCPU1.Y33 (VCCGT), JCPU1.Y34 (VCCGT), JCPU1.Y36 (VCCGT), JCPU1.Y38 (VCCGT)
VDDQ: JCPU1.AT18 (VDDQ), JCPU1.AT21 (VDDQ), JCPU1.AU13 (VDDQ), JCPU1.AU15 (VDDQ), JCPU1.AU19 (VDDQ), JCPU1.AU23 (VDDQ), JCPU1.AV11 (VDDQ), JCPU1.AV17 (VDDQ), JCPU1.AV21 (VDDQ), JCPU1.AW10 (VDDQ), JCPU1.AW14 (VDDQ), JCPU1.AW25 (VDDQ), JCPU1.AY12 (VDDQ), JCPU1.AY16 (VDDQ), JCPU1.AY18 (VDDQ), JCPU1.AY23 (VDDQ)

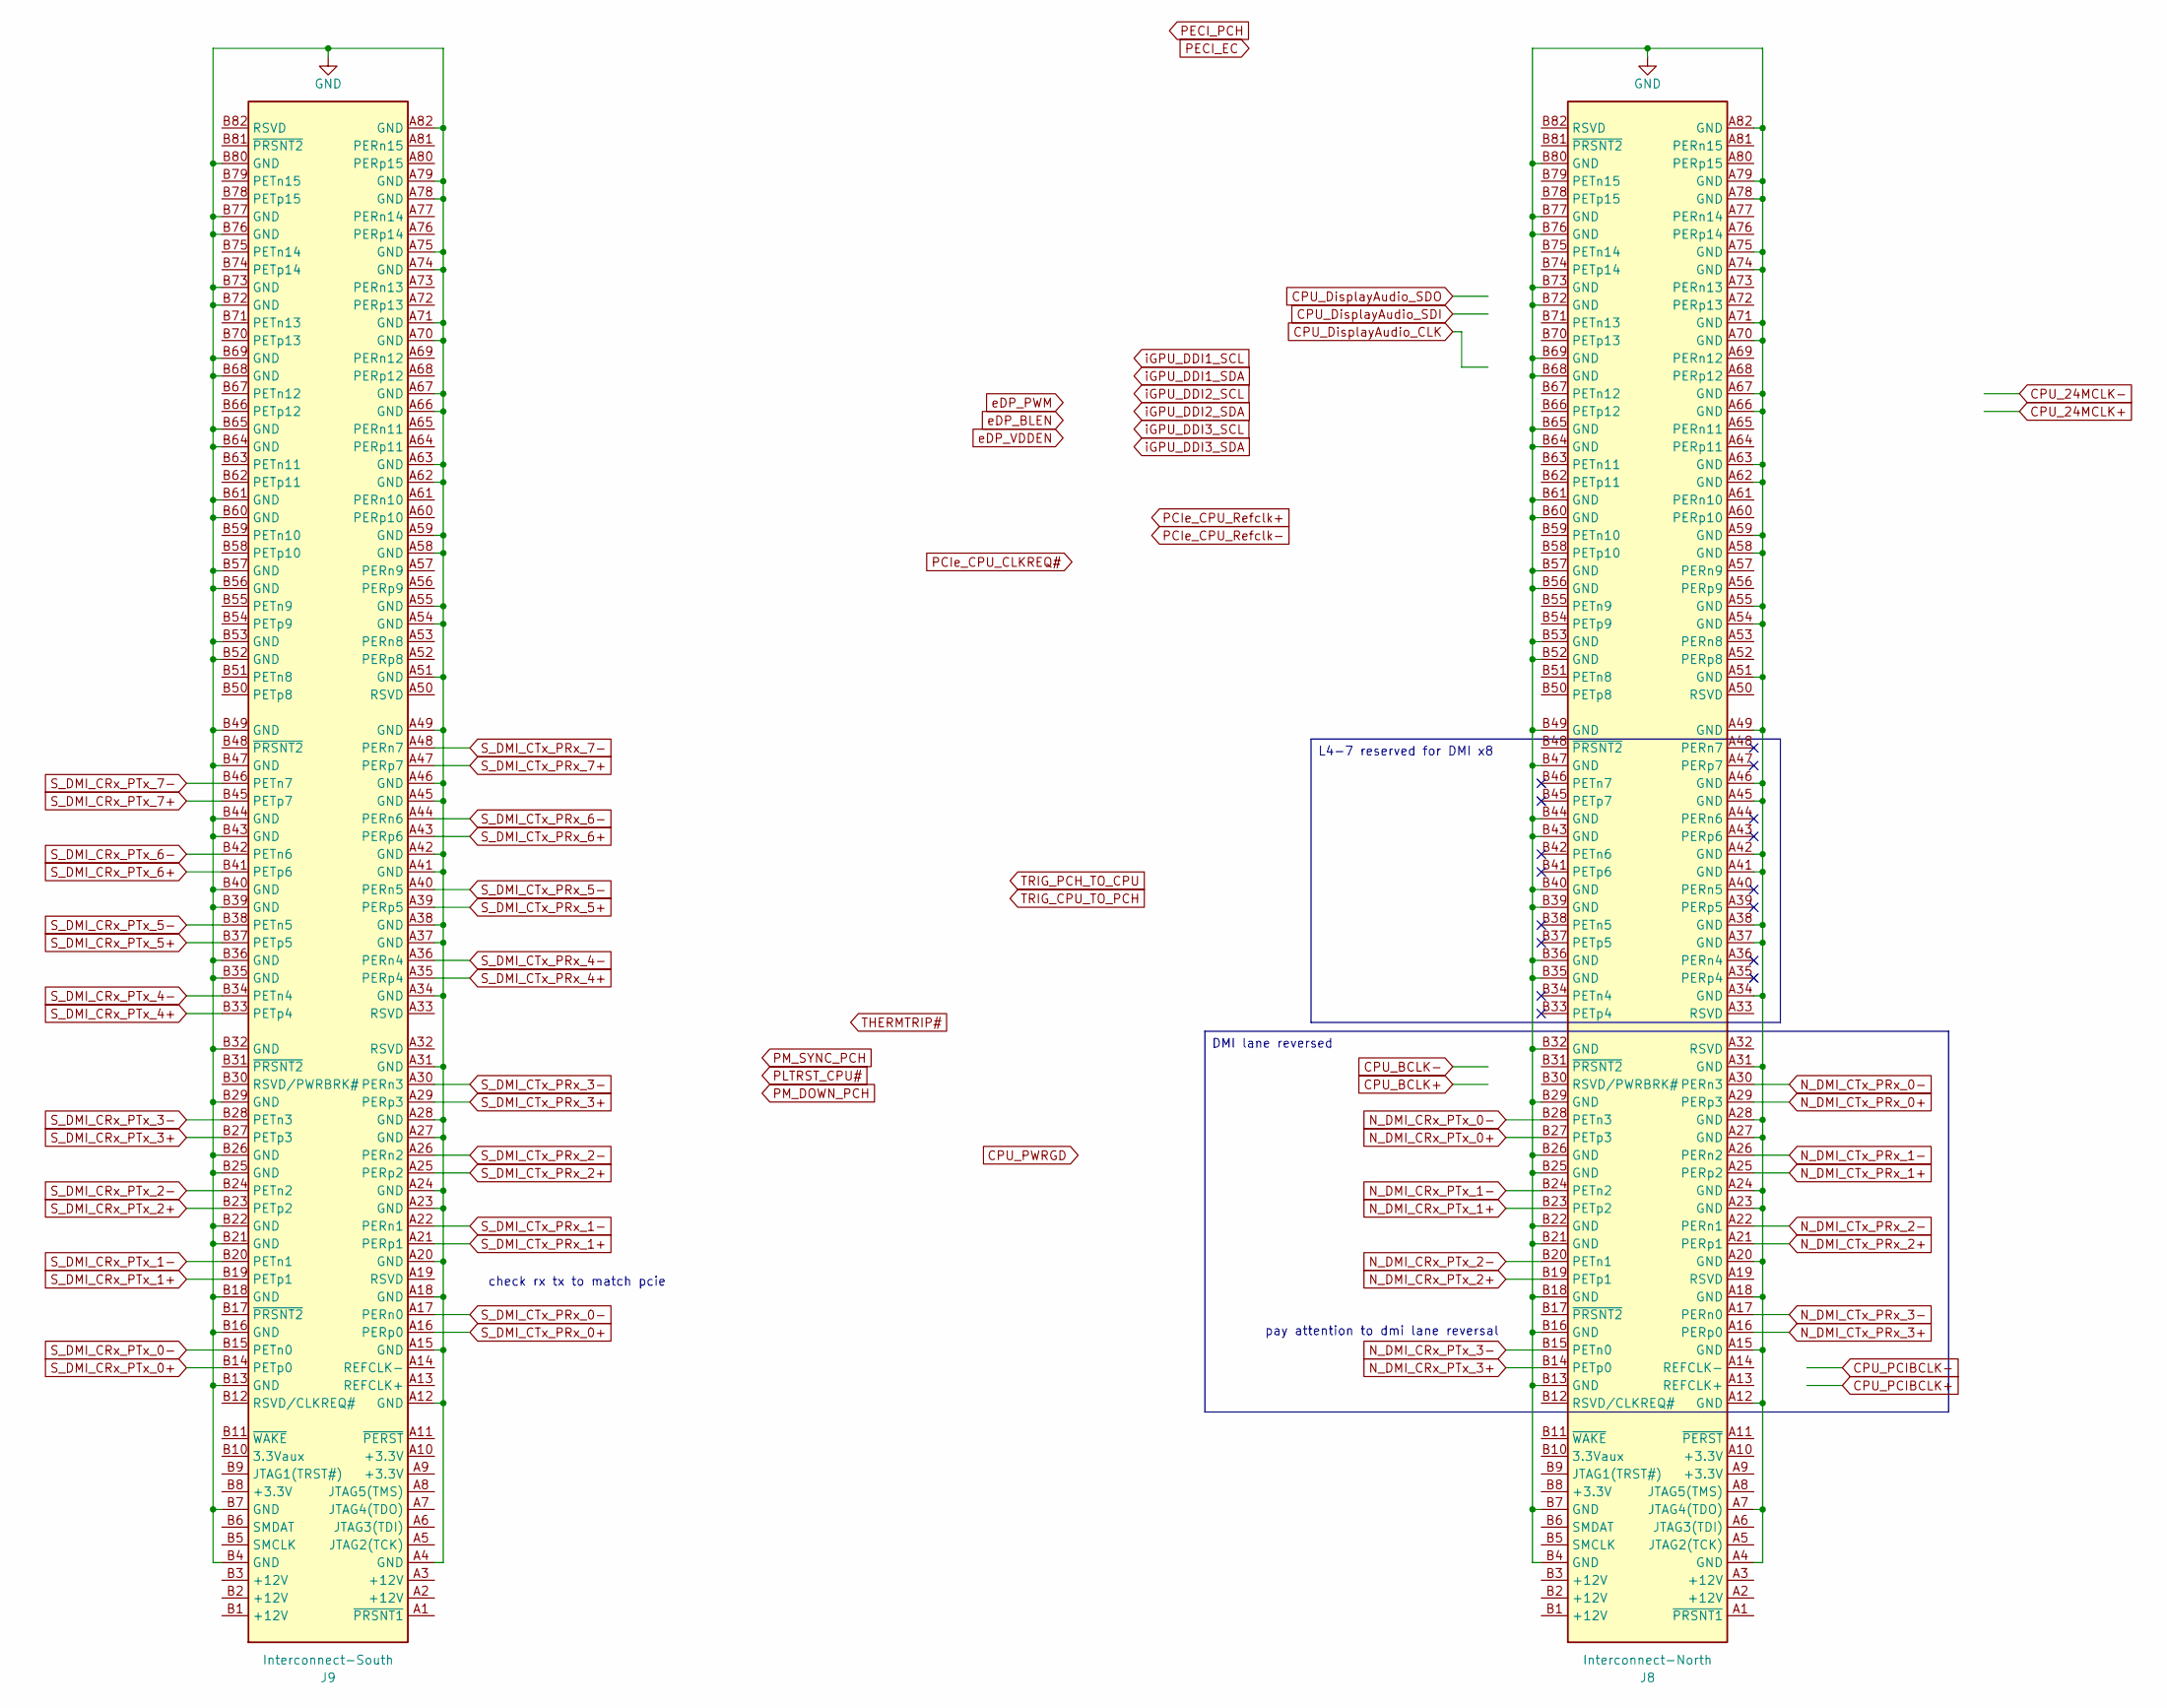
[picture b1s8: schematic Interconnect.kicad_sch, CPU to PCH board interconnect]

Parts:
J8: Interconnect-North; PCIe_x16_straddlemount
J9: Interconnect-South; BUS_PCIexpress_x16

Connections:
GND: J8.A4 (GND), J8.A7 (JTAG4(TDO)), J8.A12 (GND), J8.A15 (GND), J8.A18 (GND), J8.A20 (GND), J8.A23 (GND), J8.A24 (GND), J8.A27 (GND), J8.A28 (GND), J8.A31 (GND), J8.A34 (GND), J8.A37 (GND), J8.A38 (GND), J8.A41 (GND), J8.A42 (GND), J8.A45 (GND), J8.A46 (GND), J8.A49 (GND), J8.A51 (GND), J8.A54 (GND), J8.A55 (GND), J8.A58 (GND), J8.A59 (GND), J8.A62 (GND), J8.A63 (GND), J8.A66 (GND), J8.A67 (GND), J8.A70 (GND), J8.A71 (GND), J8.A74 (GND), J8.A75 (GND), J8.A78 (GND), J8.A79 (GND), J8.A82 (GND), J8.B4 (GND), J8.B7 (GND), J8.B13 (GND), J8.B16 (GND), J8.B18 (GND), J8.B21 (GND), J8.B22 (GND), J8.B25 (GND), J8.B26 (GND), J8.B29 (GND), J8.B32 (GND), J8.B35 (GND), J8.B36 (GND), J8.B39 (GND), J8.B40 (GND), J8.B43 (GND), J8.B44 (GND), J8.B47 (GND), J8.B49 (GND), J8.B52 (GND), J8.B53 (GND), J8.B56 (GND), J8.B57 (GND), J8.B60 (GND), J8.B61 (GND), J8.B64 (GND), J8.B65 (GND), J8.B68 (GND), J8.B69 (GND), J8.B72 (GND), J8.B73 (GND), J8.B76 (GND), J8.B77 (GND), J8.B80 (GND), J9.A4 (GND), J9.A12 (GND), J9.A15 (GND), J9.A18 (GND), J9.A20 (GND), J9.A23 (GND), J9.A24 (GND), J9.A27 (GND), J9.A28 (GND), J9.A31 (GND), J9.A34 (GND), J9.A37 (GND), J9.A38 (GND), J9.A41 (GND), J9.A42 (GND), J9.A45 (GND), J9.A46 (GND), J9.A49 (GND), J9.A51 (GND), J9.A54 (GND), J9.A55 (GND), J9.A58 (GND), J9.A59 (GND), J9.A62 (GND), J9.A63 (GND), J9.A66 (GND), J9.A67 (GND), J9.A70 (GND), J9.A71 (GND), J9.A74 (GND), J9.A75 (GND), J9.A78 (GND), J9.A79 (GND), J9.A82 (GND), J9.B4 (GND), J9.B7 (GND), J9.B13 (GND), J9.B16 (GND), J9.B18 (GND), J9.B21 (GND), J9.B22 (GND), J9.B25 (GND), J9.B26 (GND), J9.B29 (GND), J9.B32 (GND), J9.B35 (GND), J9.B36 (GND), J9.B39 (GND), J9.B40 (GND), J9.B43 (GND), J9.B44 (GND), J9.B47 (GND), J9.B49 (GND), J9.B52 (GND), J9.B53 (GND), J9.B56 (GND), J9.B57 (GND), J9.B60 (GND), J9.B61 (GND), J9.B64 (GND)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; also elsewhere on the board
N_DMI_CRx_PTx_0+: J8.B27 (PETp3); also elsewhere on the board
N_DMI_CRx_PTx_0-: J8.B28 (PETn3); also elsewhere on the board
N_DMI_CRx_PTx_1+: J8.B23 (PETp2); also elsewhere on the board
N_DMI_CRx_PTx_1-: J8.B24 (PETn2); also elsewhere on the board
N_DMI_CRx_PTx_2+: J8.B19 (PETp1); also elsewhere on the board
N_DMI_CRx_PTx_2-: J8.B20 (PETn1); also elsewhere on the board
N_DMI_CRx_PTx_3+: J8.B14 (PETp0); also elsewhere on the board
N_DMI_CRx_PTx_3-: J8.B15 (PETn0); also elsewhere on the board
N_DMI_CTx_PRx_0+: J8.A29 (PERp3); also elsewhere on the board
N_DMI_CTx_PRx_0-: J8.A30 (PERn3); also elsewhere on the board
N_DMI_CTx_PRx_1+: J8.A25 (PERp2); also elsewhere on the board
N_DMI_CTx_PRx_1-: J8.A26 (PERn2); also elsewhere on the board
N_DMI_CTx_PRx_2+: J8.A21 (PERp1); also elsewhere on the board
N_DMI_CTx_PRx_2-: J8.A22 (PERn1); also elsewhere on the board
N_DMI_CTx_PRx_3+: J8.A16 (PERp0); also elsewhere on the board
N_DMI_CTx_PRx_3-: J8.A17 (PERn0); also elsewhere on the board
S_DMI_CRx_PTx_0+: J9.B14 (PETp0); also elsewhere on the board
S_DMI_CRx_PTx_0-: J9.B15 (PETn0); also elsewhere on the board
S_DMI_CRx_PTx_1+: J9.B19 (PETp1); also elsewhere on the board
S_DMI_CRx_PTx_1-: J9.B20 (PETn1); also elsewhere on the board
S_DMI_CRx_PTx_2+: J9.B23 (PETp2); also elsewhere on the board
S_DMI_CRx_PTx_2-: J9.B24 (PETn2); also elsewhere on the board
S_DMI_CRx_PTx_3+: J9.B27 (PETp3); also elsewhere on the board
S_DMI_CRx_PTx_3-: J9.B28 (PETn3); also elsewhere on the board
S_DMI_CRx_PTx_4+: J9.B33 (PETp4); also elsewhere on the board
S_DMI_CRx_PTx_4-: J9.B34 (PETn4); also elsewhere on the board
S_DMI_CRx_PTx_5+: J9.B37 (PETp5); also elsewhere on the board
S_DMI_CRx_PTx_5-: J9.B38 (PETn5); also elsewhere on the board
S_DMI_CRx_PTx_6+: J9.B41 (PETp6); also elsewhere on the board
S_DMI_CRx_PTx_6-: J9.B42 (PETn6); also elsewhere on the board
S_DMI_CRx_PTx_7+: J9.B45 (PETp7); also elsewhere on the board
S_DMI_CRx_PTx_7-: J9.B46 (PETn7); also elsewhere on the board
S_DMI_CTx_PRx_0+: J9.A16 (PERp0); also elsewhere on the board
S_DMI_CTx_PRx_0-: J9.A17 (PERn0); also elsewhere on the board
S_DMI_CTx_PRx_1+: J9.A21 (PERp1); also elsewhere on the board
S_DMI_CTx_PRx_1-: J9.A22 (PERn1); also elsewhere on the board
S_DMI_CTx_PRx_2+: J9.A25 (PERp2); also elsewhere on the board
S_DMI_CTx_PRx_2-: J9.A26 (PERn2); also elsewhere on the board
S_DMI_CTx_PRx_3+: J9.A29 (PERp3); also elsewhere on the board
S_DMI_CTx_PRx_3-: J9.A30 (PERn3); also elsewhere on the board
S_DMI_CTx_PRx_4+: J9.A35 (PERp4); also elsewhere on the board
S_DMI_CTx_PRx_4-: J9.A36 (PERn4); also elsewhere on the board
S_DMI_CTx_PRx_5+: J9.A39 (PERp5); also elsewhere on the board
S_DMI_CTx_PRx_5-: J9.A40 (PERn5); also elsewhere on the board
S_DMI_CTx_PRx_6+: J9.A43 (PERp6); also elsewhere on the board
S_DMI_CTx_PRx_6-: J9.A44 (PERn6); also elsewhere on the board
S_DMI_CTx_PRx_7+: J9.A47 (PERp7); also elsewhere on the board
S_DMI_CTx_PRx_7-: J9.A48 (PERn7); also elsewhere on the board

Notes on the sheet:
pay attention to dmi lane reversal
check rx tx to match pcie
L4-7 reserved for DMI x8
DMI lane reversed

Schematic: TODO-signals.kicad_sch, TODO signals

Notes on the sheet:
connect from CPU vrom VR READY signal to CPU? with some control based on sleep state? look into more when building vrm
This page contains notes about signals I've researched the purpose and functionality of but not yet implemented
Controls enable pin on memory power supply VTT (ACC bus termination) rail, seeing different implementations but each at least buffers or inverts the signal a few times output from CPU, high means power on, low means power off
